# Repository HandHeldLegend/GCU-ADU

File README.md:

# GCU-ADU
A template KiCad file to create add-on flex PCBs for the GC Ultimate

## NOTES
There is a stiffener layer. The total thickness of the FPC plus the stiffener layer MUST be 0.3mm. Please ensure this matches according to whichever PCB fabrication house you use.

There is also an adhesive layer that is optional but recommended. to help secure the PCB in place.

The Switches are placeholder and you will likely need to make modifications to ensure your PCB will contain the appropriate switches.

Cutouts for the RGB LEDs are present here. Do not cover those as it will complicate the install process. Assume that any cutouts here are 100% necessary and should not be tampered with. 

This example file is designed to be used with 2.5mm height tactile switches, in combination with 5mm diameter, 2mm height silicone adhesive stoppers.

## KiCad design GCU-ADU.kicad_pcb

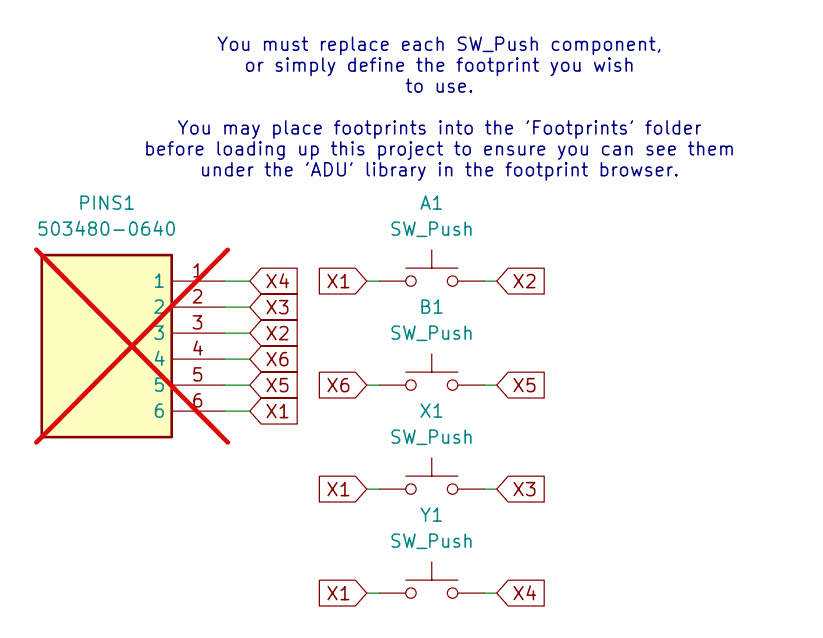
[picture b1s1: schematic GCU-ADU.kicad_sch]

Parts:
A1: SW_Push; EVQ-Q2F02W; MPN EVQ-Q2F02W; LCSC C388887
B1: SW_Push; EVQ-Q2F02W; MPN EVQ-Q2F02W; LCSC C388887
PINS1: 503480-0640; molex_5034800640_ribbon; Mouser Part Number 538-503480-0640; not fitted
X1: SW_Push; EVQ-Q2F02W; MPN EVQ-Q2F02W; LCSC C388887
Y1: SW_Push; EVQ-Q2F02W; MPN EVQ-Q2F02W; LCSC C388887

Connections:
X1: A1.1, PINS1.6, X1.1, Y1.1
X2: A1.2, PINS1.3
X3: PINS1.2, X1.2
X4: PINS1.1, Y1.2
X5: B1.2, PINS1.5
X6: B1.1, PINS1.4

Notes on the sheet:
You must replace each SW_Push component, or simply define the footprint you wish to use. You may place footprints into the 'Footprints' folder before loading up this project to ensure you can see them under the 'ADU' library in the footprint browser.

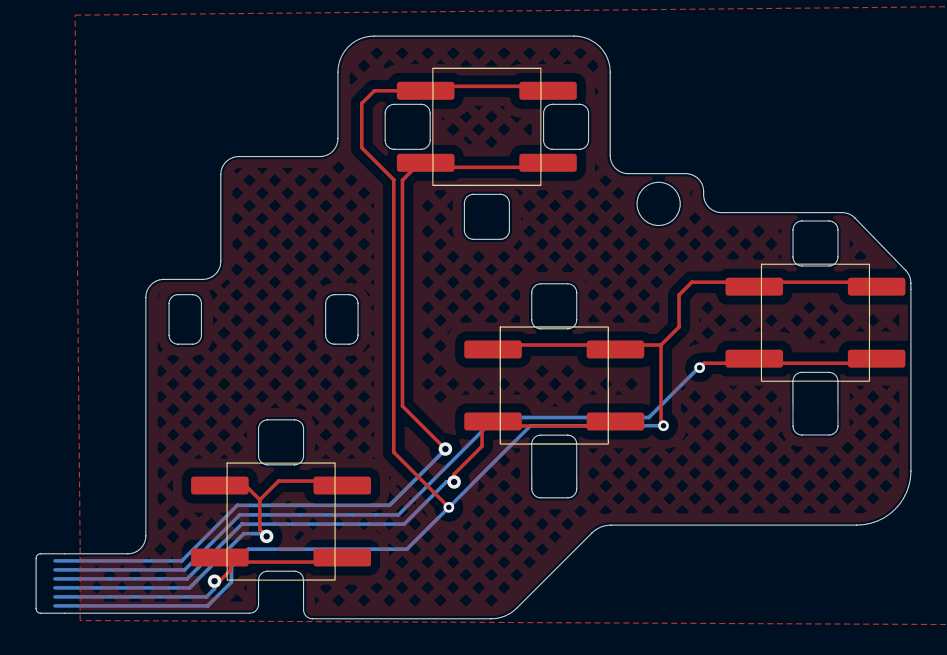
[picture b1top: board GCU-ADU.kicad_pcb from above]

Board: 2 copper layers, 48.6 x 32.4 mm, 5 parts (1 on the bottom side), 6 nets.

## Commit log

2025-08-15 Resolve backwards connector pins
2025-08-17 Update
    - Update with proper switches
2025-08-18 Update adhesive layer
